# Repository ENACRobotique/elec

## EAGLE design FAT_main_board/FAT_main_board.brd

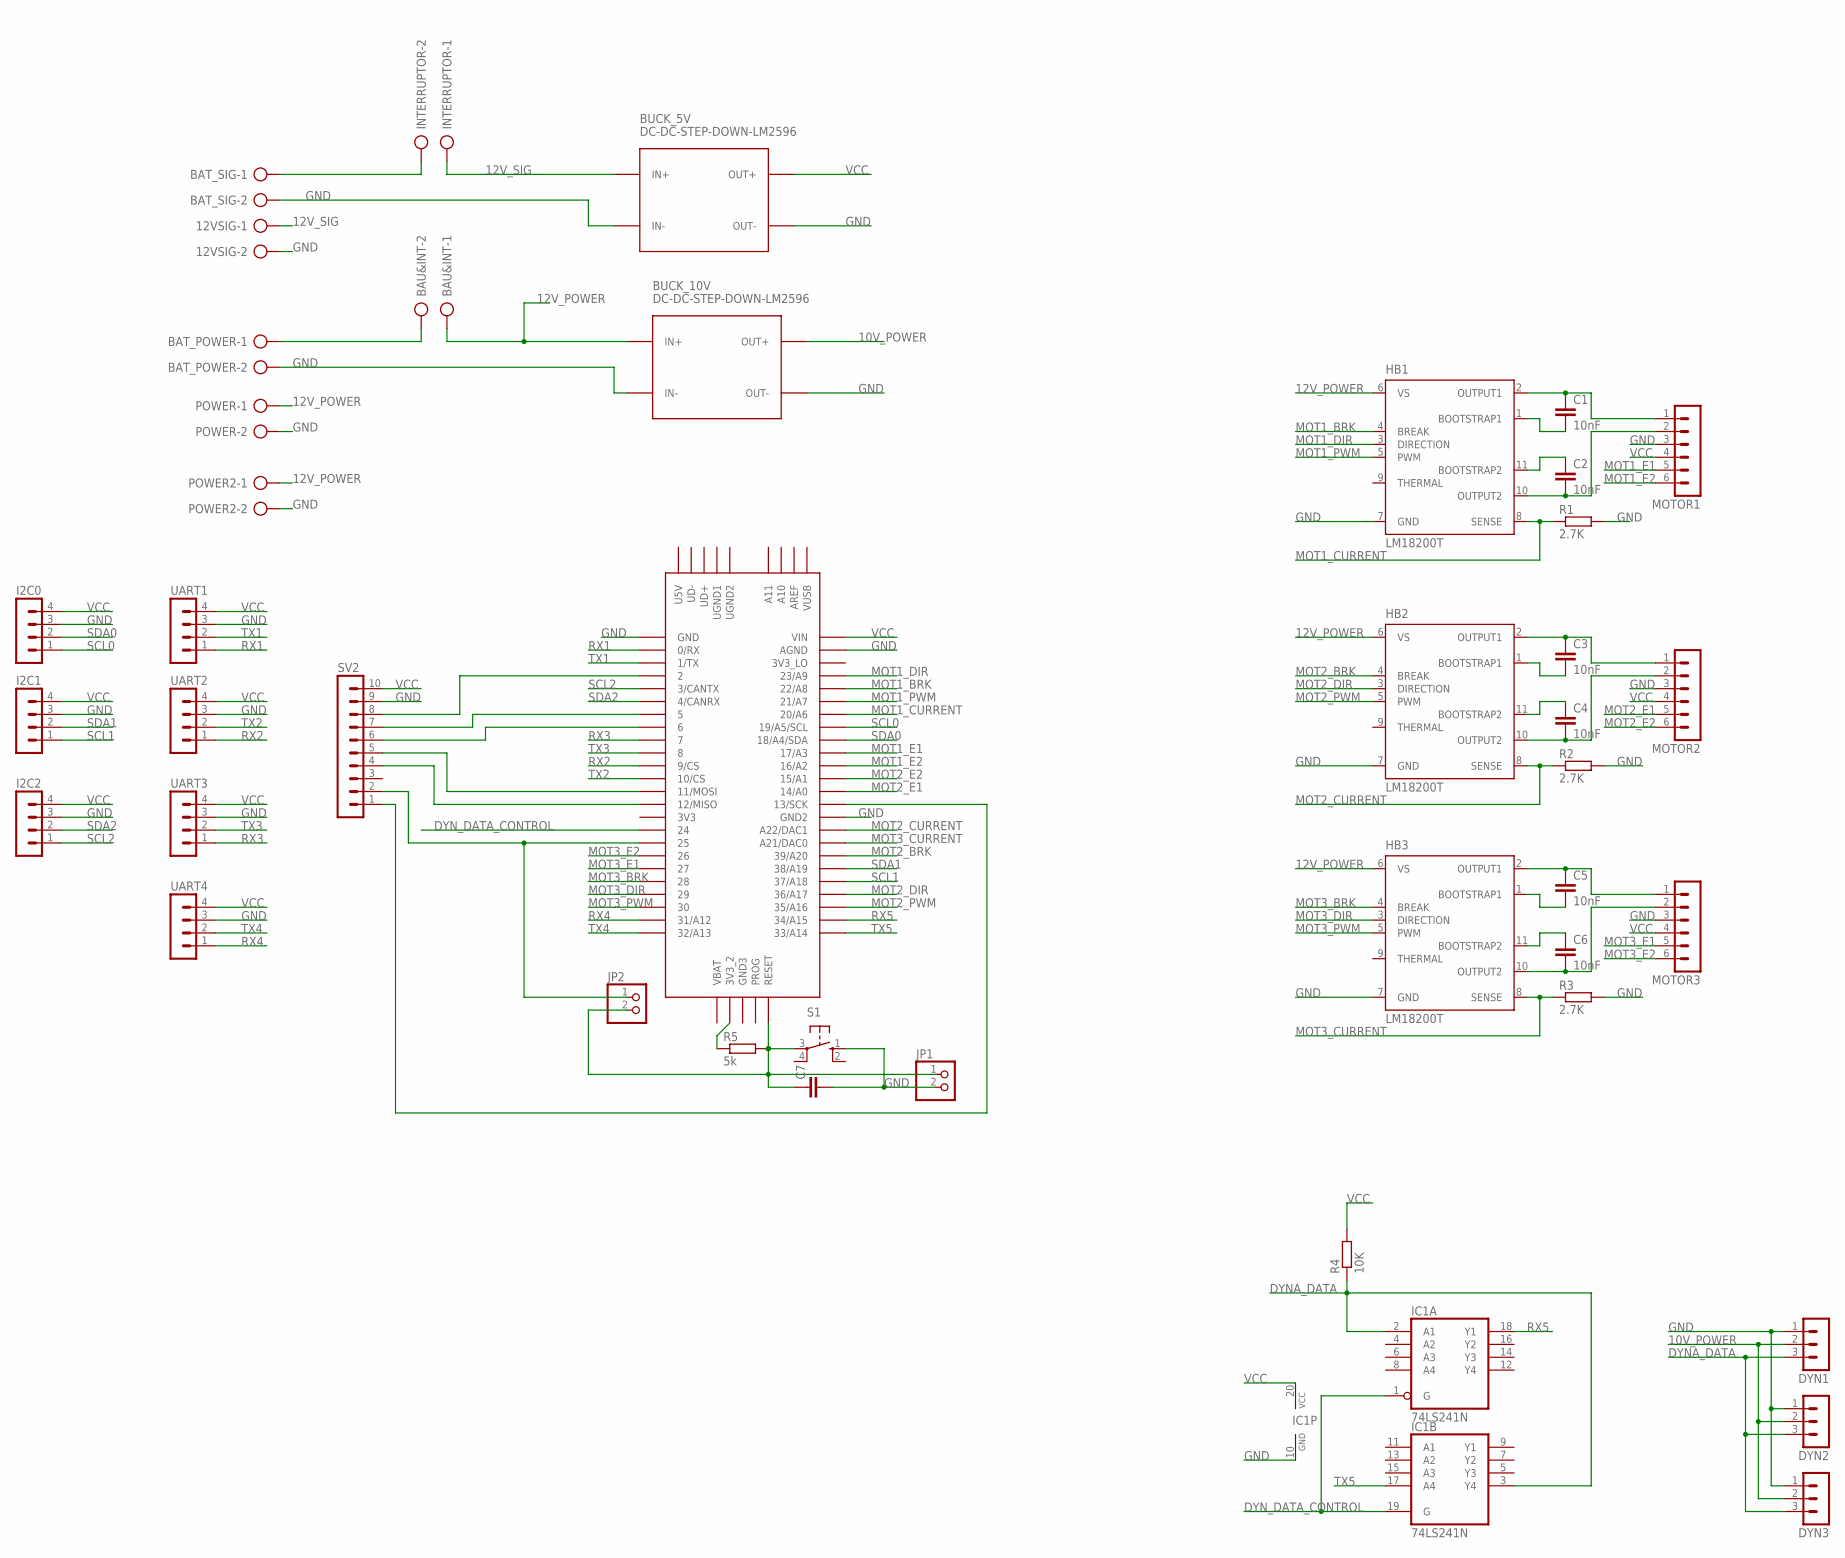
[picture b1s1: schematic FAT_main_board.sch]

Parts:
12VSIG: AK300/2
BAT_POWER: AK300/2
BAT_SIG: AK300/2
BAU&INT: AK300/2
BUCK_5V, BUCK_10V: DC-DC-STEP-DOWN-LM2596
C1, C2, C3, C4, C5, C6: 10nF; C050-035X075
C7: C-EU025-025X050; C025-025X050
DYN1, DYN2, DYN3: MA03-1
HB1, HB2, HB3: LM18200T; TO-220-11
I2C0, I2C1, I2C2: MA04-1
IC1: 74LS241N; DIL20
INTERRUPTOR: AK300/2
JP1, JP2: PINHD-1X2; 1X02
MOTOR1, MOTOR2, MOTOR3: MA06-1
POWER, POWER2: AK300/2
R1, R2, R3: 2.7K; 0204/7
R4: 10K; 0204/7
R5: 5k; 0204/7
S1: 10-XX; B3F-10XX
SV2: MA10-1
U$1: TEENSY_3.5/3.6
UART1, UART2, UART3, UART4: MA04-1

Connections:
10V_POWER: BUCK_10V.OUT+, DYN1.2, DYN2.2, DYN3.2
12V_POWER: BAU&INT.1, BUCK_10V.IN+, HB1.6 (VS), HB2.6 (VS), HB3.6 (VS), POWER.1, POWER2.1
12V_SIG: 12VSIG.1, BUCK_5V.IN+, INTERRUPTOR.1
DYNA_DATA: DYN1.3, DYN2.3, DYN3.3, IC1.2 (A1), IC1.3 (Y4), R4.1
DYN_DATA_CONTROL: IC1.1 (G), IC1.19 (G), U$1.24
GND: 12VSIG.2, BAT_POWER.2, BAT_SIG.2, BUCK_5V.IN-, BUCK_5V.OUT-, BUCK_10V.IN-, BUCK_10V.OUT-, C7.2, DYN1.1, DYN2.1, DYN3.1, HB1.7 (GND), HB2.7 (GND), HB3.7 (GND), I2C0.3, I2C1.3, I2C2.3, IC1.10 (GND), JP1.2, MOTOR1.3, MOTOR2.3, MOTOR3.3, POWER.2, POWER2.2, R1.2, R2.2, R3.2, S1.1 (S), SV2.9, U$1.AGND, U$1.GND, U$1.GND2, UART1.3, UART2.3, UART3.3, UART4.3
MOT1_BRK: HB1.4 (BREAK), U$1.22/A8
MOT1_CURRENT: HB1.8 (SENSE), R1.1, U$1.20/A6
MOT1_DIR: HB1.3 (DIRECTION), U$1.23/A9
MOT1_E1: MOTOR1.5, U$1.17/A3
MOT1_E2: MOTOR1.6, U$1.16/A2
MOT1_PWM: HB1.5 (PWM), U$1.21/A7
MOT2_BRK: HB2.4 (BREAK), U$1.39/A20
MOT2_CURRENT: HB2.8 (SENSE), R2.1, U$1.A22/DAC1
MOT2_DIR: HB2.3 (DIRECTION), U$1.36/A17
MOT2_E1: MOTOR2.5, U$1.14/A0
MOT2_E2: MOTOR2.6, U$1.15/A1
MOT2_PWM: HB2.5 (PWM), U$1.35/A16
MOT3_BRK: HB3.4 (BREAK), U$1.28
MOT3_CURRENT: HB3.8 (SENSE), R3.1, U$1.21/DAC0 (A21/DAC0)
MOT3_DIR: HB3.3 (DIRECTION), U$1.29
MOT3_E1: MOTOR3.5, U$1.27
MOT3_E2: MOTOR3.6, U$1.26
MOT3_PWM: HB3.5 (PWM), U$1.30
unnamed: C1.1, HB1.2 (OUTPUT1), MOTOR1.1
unnamed: C2.2, HB1.10 (OUTPUT2), MOTOR1.2
unnamed: C1.2, HB1.1 (BOOTSTRAP1)
unnamed: C2.1, HB1.11 (BOOTSTRAP2)
unnamed: C3.1, HB2.2 (OUTPUT1), MOTOR2.1
unnamed: C3.2, HB2.1 (BOOTSTRAP1)
unnamed: C4.1, HB2.11 (BOOTSTRAP2)
unnamed: C4.2, HB2.10 (OUTPUT2), MOTOR2.2
unnamed: SV2.7, U$1.5
unnamed: SV2.6, U$1.6
unnamed: SV2.5, U$1.11/MOSI
unnamed: SV2.4, U$1.12/MISO
unnamed: BAT_POWER.1, BAU&INT.2
unnamed: C5.1, HB3.2 (OUTPUT1), MOTOR3.1
unnamed: C5.2, HB3.1 (BOOTSTRAP1)
unnamed: C6.1, HB3.11 (BOOTSTRAP2)
unnamed: C6.2, HB3.10 (OUTPUT2), MOTOR3.2
unnamed: SV2.8, U$1.2
unnamed: C7.1, JP1.1, JP2.2, R5.2, S1.3, U$1.RESET
unnamed: BAT_SIG.1, INTERRUPTOR.2
unnamed: SV2.1, U$1.13/SCK
unnamed: R5.1, U$1.3V3_2
unnamed: JP2.1, SV2.2, U$1.25
RX1: U$1.0/RX, UART1.1
RX2: U$1.9/CS, UART2.1
RX3: U$1.7, UART3.1
RX4: U$1.31/A12, UART4.1
RX5: IC1.18 (Y1), U$1.34/A15
SCL0: I2C0.1, U$1.19/A5/SCL
SCL1: I2C1.1, U$1.37/A18
SCL2: I2C2.1, U$1.3/CANTX
SDA0: I2C0.2, U$1.18/A4/SDA
SDA1: I2C1.2, U$1.38/A19
SDA2: I2C2.2, U$1.4/CANRX
TX1: U$1.1/TX, UART1.2
TX2: U$1.10/CS, UART2.2
TX3: U$1.8, UART3.2
TX4: U$1.32/A13, UART4.2
TX5: IC1.17 (A4), U$1.33/A14
VCC: BUCK_5V.OUT+, I2C0.4, I2C1.4, I2C2.4, IC1.20 (VCC), MOTOR1.4, MOTOR2.4, MOTOR3.4, R4.2, SV2.10, U$1.VIN, UART1.4, UART2.4, UART3.4, UART4.4

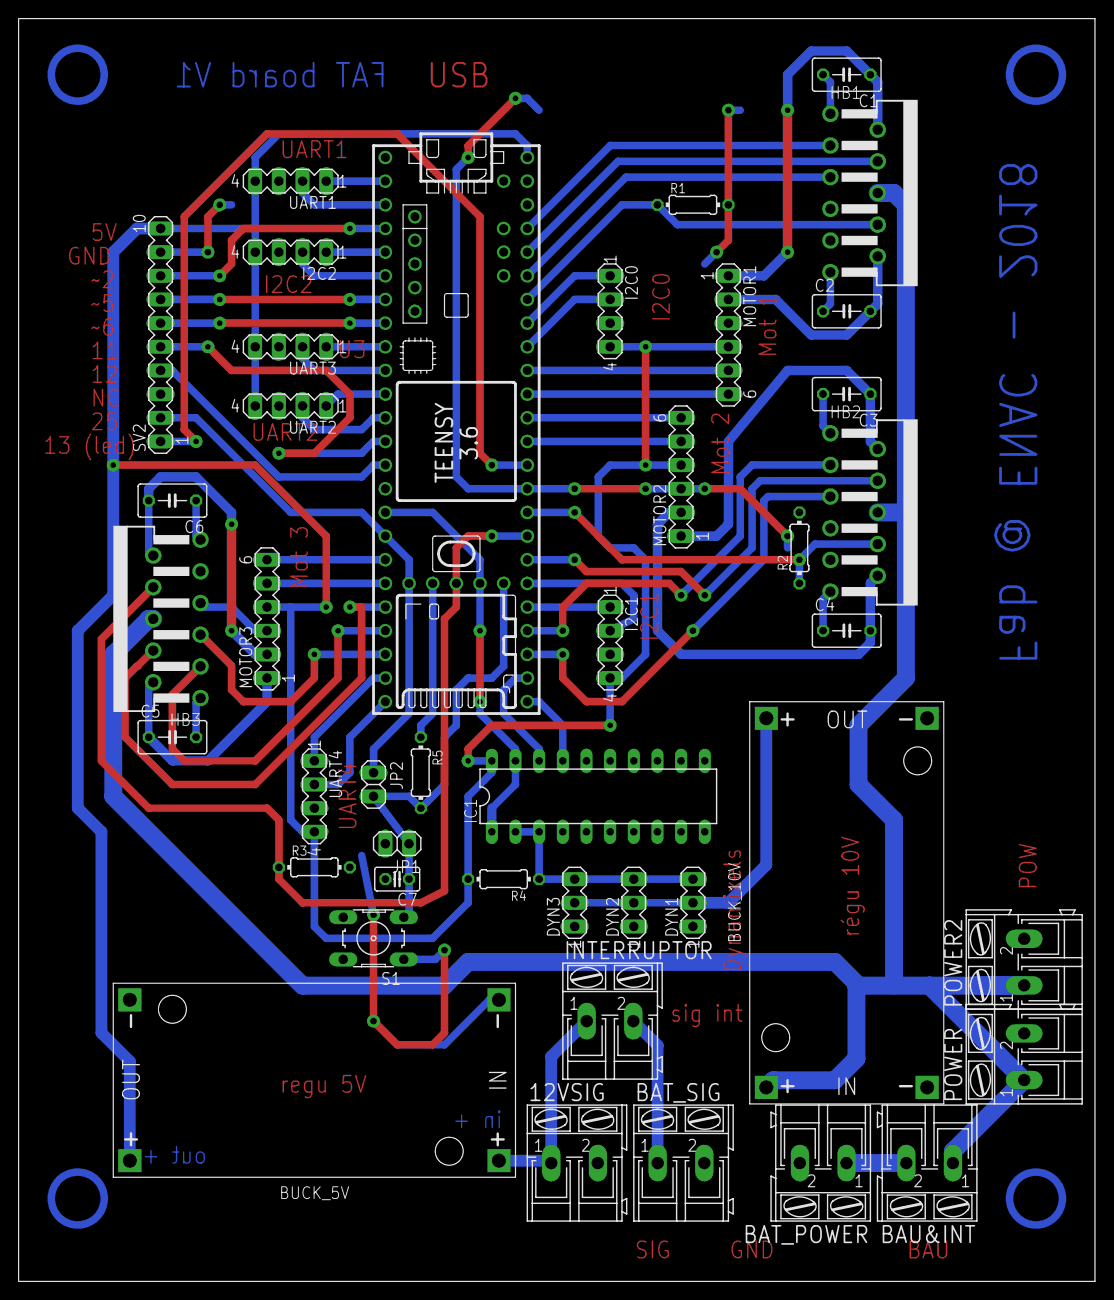
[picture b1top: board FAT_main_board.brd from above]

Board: 2 copper layers, 115.5 x 135.6 mm, 43 parts (0 on the bottom side), 64 nets.

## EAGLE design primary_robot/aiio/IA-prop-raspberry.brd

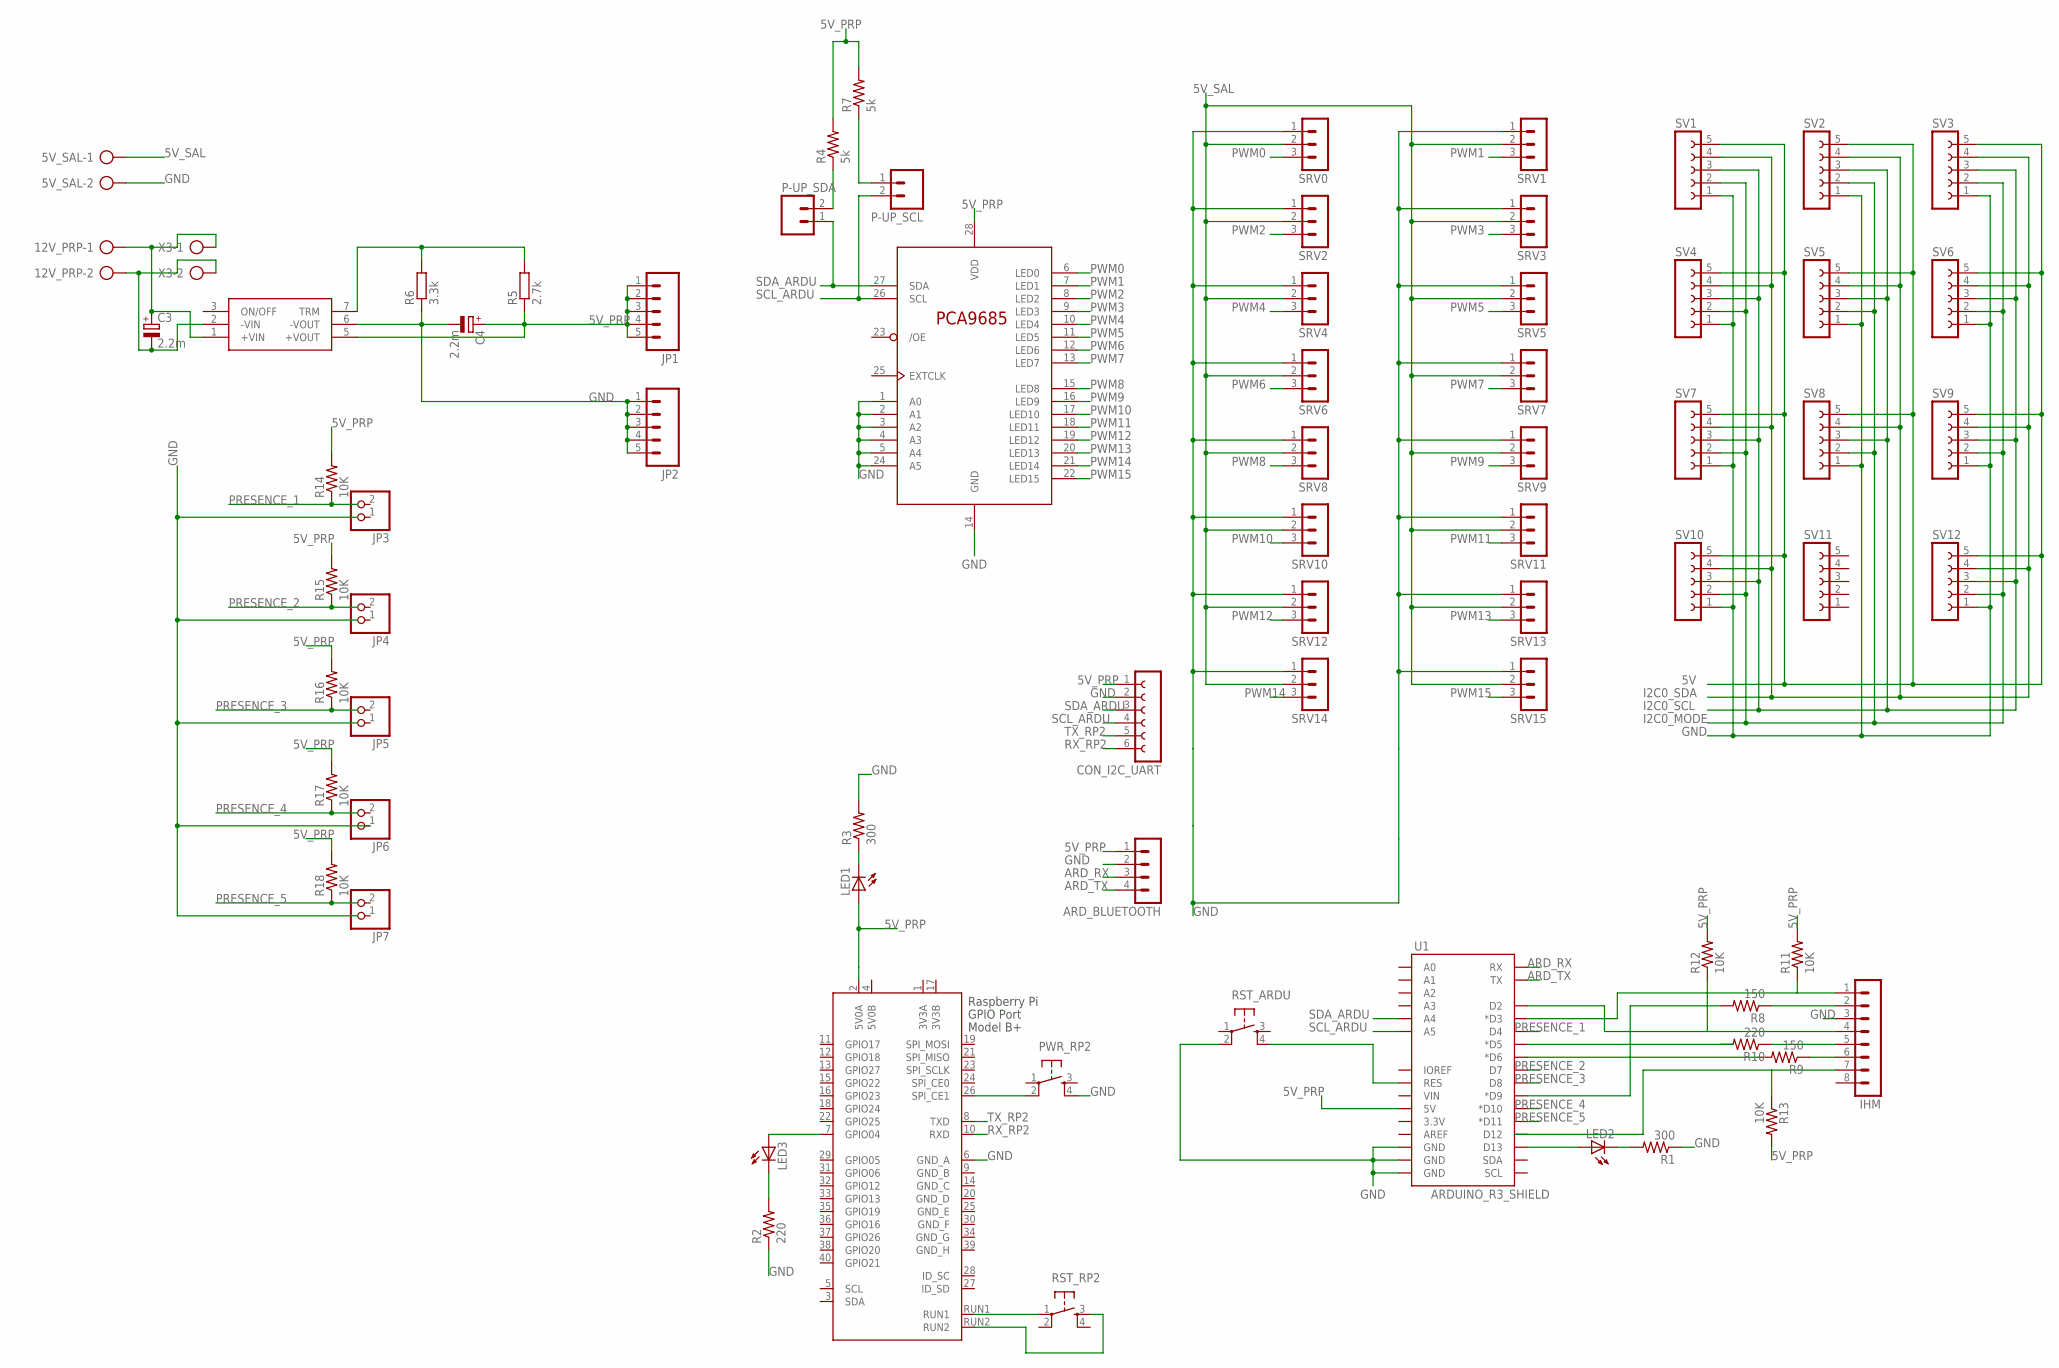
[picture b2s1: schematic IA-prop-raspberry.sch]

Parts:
5V_SAL, 12V_PRP: AK300/2
ARD_BLUETOOTH: MA04-1
C3, C4: 2.2m; E5-13
CON_I2C_UART: FE06-1; FE06
IHM: MA08-1
JP1, JP2: M05PTH; 1X05
JP3, JP4, JP5, JP6, JP7: PINHD-1X2; 1X02
LED1, LED2, LED3: LED3MM
P-UP_SCL: M02PTH; 1X02
P-UP_SDA: M02PTH; 1X02
PWR_RP2: TAC_SWITCHPTH; TACTILE-PTH
R1, R3: 300; AXIAL-0.3
R2, R10: 220; AXIAL-0.3
R4, R7: 5k; AXIAL-0.3
R5: 2.7k; 0207/7
R6: 3.3k; 0207/7
R8, R9: 150; AXIAL-0.3
R11, R12, R13, R14, R15, R16, R17, R18: 10K; AXIAL-0.3
RP2: RASPI_BOARD_B+#_FP; RASPI_BOARD_B+_FULL_PAD
RST_ARDU: TAC_SWITCHPTH; TACTILE-PTH
RST_RP2: TAC_SWITCHPTH; TACTILE-PTH
SRV0, SRV1, SRV2, SRV3, SRV4, SRV5, SRV6, SRV7, SRV8, SRV9, SRV10, SRV11, SRV12, SRV13, SRV14, SRV15: MA03-1
SV1, SV2, SV3, SV4, SV5, SV6, SV7, SV8, SV9, SV10, SV11, SV12: FE05-1
U1: ARDUINO_R3_SHIELD; UNO_R3_SHIELD
U$1: PCA9685PW; TSSOP28
U$2: TEN25-1211TEN25-1211; TEN25
X3: AK300/2

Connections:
3V3A: RP2.1 (3V3A)
3V3B: RP2.17 (3V3B)
5V: SV1.5, SV2.5, SV3.5, SV4.5, SV5.5, SV6.5, SV7.5, SV8.5, SV9.5, SV10.5, SV12.5
5V0B: RP2.4 (5V0B)
5V_PRP: ARD_BLUETOOTH.1, C4.+, CON_I2C_UART.1, JP1.1, JP1.2, JP1.3, JP1.4, JP1.5, LED1.A, R4.P$2 (2), R5.1, R7.P$2 (2), R11.P$2 (2), R12.P$2 (2), R13.P$2 (2), R14.P$2 (2), R15.P$2 (2), R16.P$2 (2), R17.P$2 (2), R18.P$2 (2), RP2.2 (5V0A), U1.5V, U$1.28 (VDD), U$2.5 (+VOUT)
5V_PRP1: LED2.A, U1.D13
5V_SAL: 5V_SAL.1, SRV0.2, SRV1.2, SRV2.2, SRV3.2, SRV4.2, SRV5.2, SRV6.2, SRV7.2, SRV8.2, SRV9.2, SRV10.2, SRV11.2, SRV12.2, SRV13.2, SRV14.2, SRV15.2
+12V: 12V_PRP.1, C3.+, U$2.1 (+VIN), X3.1
ARD_RX: ARD_BLUETOOTH.3, U1.RX
ARD_TX: ARD_BLUETOOTH.4, U1.TX
GND: 5V_SAL.2, ARD_BLUETOOTH.2, C4.-, CON_I2C_UART.2, IHM.3, JP2.1, JP2.2, JP2.3, JP2.4, JP2.5, JP6.1, PWR_RP2.4, R1.P$1 (1), R2.P$1 (1), R3.P$2 (2), R6.1, RP2.6 (GND_A), RST_ARDU.2, SRV0.1, SRV1.1, SRV2.1, SRV3.1, SRV4.1, SRV5.1, SRV6.1, SRV7.1, SRV8.1, SRV9.1, SRV10.1, SRV11.1, SRV12.1, SRV13.1, SRV14.1, SRV15.1, SV1.1, SV2.1, SV3.1, SV4.1, SV5.1, SV6.1, SV7.1, SV8.1, SV9.1, SV10.1, SV12.1, U1.GND@0 (GND), U1.GND@1 (GND), U1.GND@2 (GND), U$1.1 (A0), U$1.2 (A1), U$1.3 (A2), U$1.4 (A3), U$1.5 (A4), U$1.14 (GND), U$1.24 (A5), U$2.6 (-VOUT)
GND_12: 12V_PRP.2, C3.-, U$2.2 (-VIN), X3.2
GND_B: RP2.9 (GND_B)
GND_C: RP2.14 (GND_C)
GND_D: RP2.20 (GND_D)
GND_E: RP2.25 (GND_E)
GND_F: RP2.30 (GND_F)
GND_G: RP2.34 (GND_G)
GND_H: RP2.39 (GND_H)
I2C0_MODE: SV1.2, SV2.2, SV3.2, SV4.2, SV5.2, SV6.2, SV7.2, SV8.2, SV9.2, SV10.2, SV12.2
I2C0_SCL: SV1.3, SV2.3, SV3.3, SV4.3, SV5.3, SV6.3, SV7.3, SV8.3, SV9.3, SV10.3, SV12.3
I2C0_SDA: SV1.4, SV2.4, SV3.4, SV4.4, SV5.4, SV6.4, SV7.4, SV8.4, SV9.4, SV10.4, SV12.4
unnamed: RP2.RUN2, RST_RP2.3
unnamed: LED2.K (C), R1.P$2 (2)
unnamed: LED3.K (C), R2.P$2 (2)
unnamed: R5.2, R6.2, U$2.7 (TRM)
unnamed: P-UP_SDA.2, R4.P$1 (1)
unnamed: LED1.K (C), R3.P$1 (1)
unnamed: RST_ARDU.4, U1.RES
unnamed: P-UP_SCL.1, R7.P$1 (1)
unnamed: R9.P$2 (2), U1.D6 (*D6)
unnamed: IHM.6, R9.P$1 (1)
unnamed: LED3.A, RP2.7 (GPIO04)
unnamed: IHM.5, R10.P$1 (1)
unnamed: IHM.2, R8.P$1 (1)
unnamed: R8.P$2 (2), U1.D9 (*D9)
unnamed: IHM.1, R11.P$1 (1), U1.D3 (*D3)
unnamed: IHM.4, R12.P$1 (1), U1.D2
unnamed: RP2.RUN1, RST_RP2.1
unnamed: IHM.7, R13.P$1 (1)
PRESENCE_1: R14.P$1 (1), U1.D4
PRESENCE_2: R15.P$1 (1), U1.D7
PRESENCE_3: R16.P$1 (1), U1.D8
PRESENCE_4: R17.P$1 (1), U1.D10 (*D10)
PRESENCE_5: R18.P$1 (1), U1.D11 (*D11)
PWM0: SRV0.3, U$1.6 (LED0)
PWM1: SRV1.3, U$1.7 (LED1)
PWM2: SRV2.3, U$1.8 (LED2)
PWM3: SRV3.3, U$1.9 (LED3)
PWM4: SRV4.3, U$1.10 (LED4)
PWM5: SRV5.3, U$1.11 (LED5)
PWM6: SRV6.3, U$1.12 (LED6)
PWM7: SRV7.3, U$1.13 (LED7)
PWM8: SRV8.3, U$1.15 (LED8)
PWM9: SRV9.3, U$1.16 (LED9)
PWM10: SRV10.3, U$1.17 (LED10)
PWM11: SRV11.3, U$1.18 (LED11)
PWM12: SRV12.3, U$1.19 (LED12)
PWM13: SRV13.3, U$1.20 (LED13)
PWM14: SRV14.3, U$1.21 (LED14)
PWM15: SRV15.3, U$1.22 (LED15)
RP2_PWR: PWR_RP2.2, RP2.26 (SPI_CE1)
RX_RP2: CON_I2C_UART.6, RP2.10 (RXD)
SCL_ARDU: CON_I2C_UART.4, P-UP_SCL.2, U1.A5, U$1.26 (SCL)
SDA_ARDU: CON_I2C_UART.3, P-UP_SDA.1, U1.A4, U$1.27 (SDA)
TX_RP2: CON_I2C_UART.5, RP2.8 (TXD)

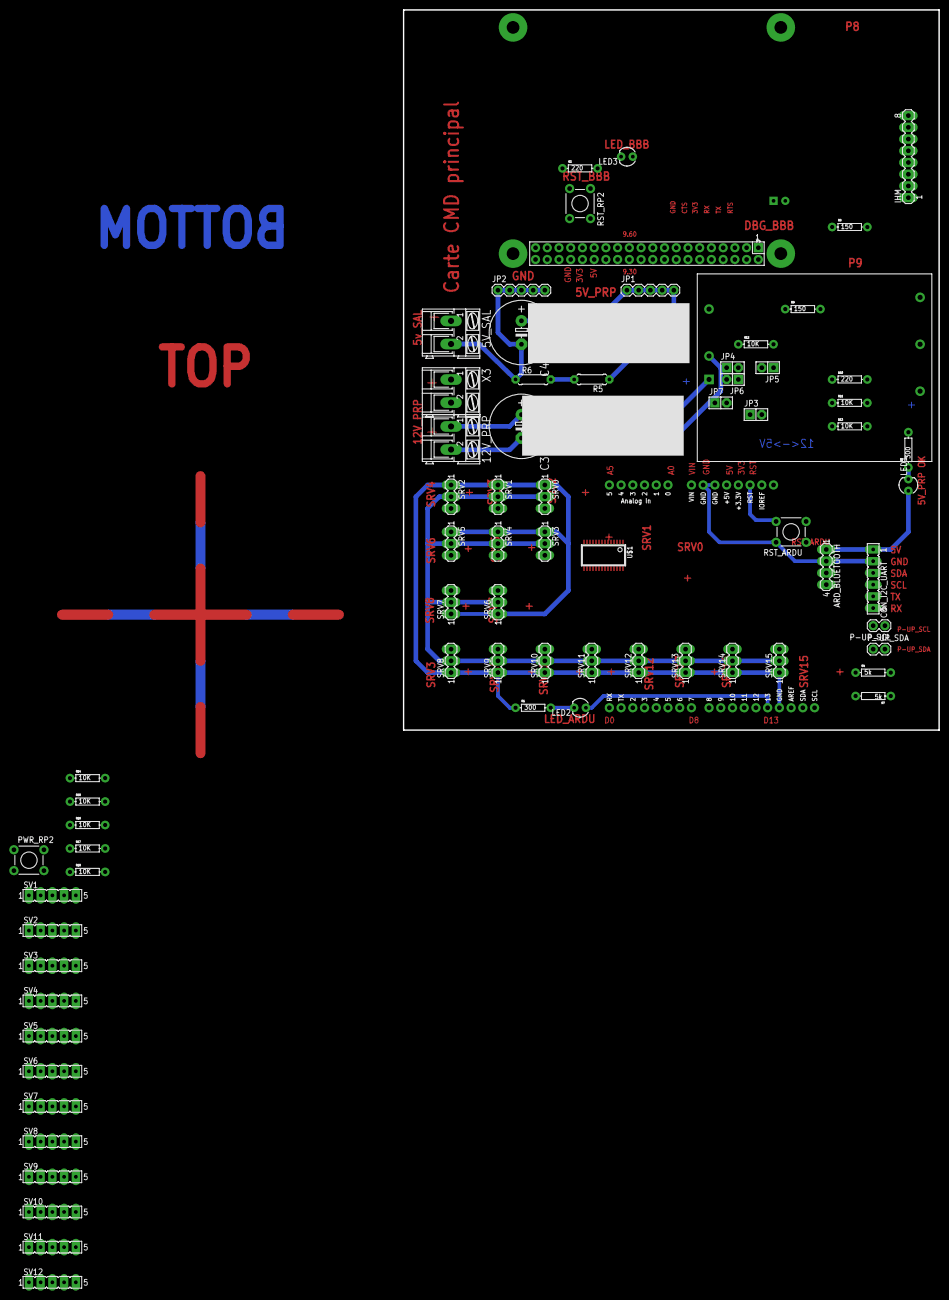
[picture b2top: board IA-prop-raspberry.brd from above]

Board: 2 copper layers, 116.0 x 156.0 mm, 73 parts (0 on the bottom side), 56 nets.

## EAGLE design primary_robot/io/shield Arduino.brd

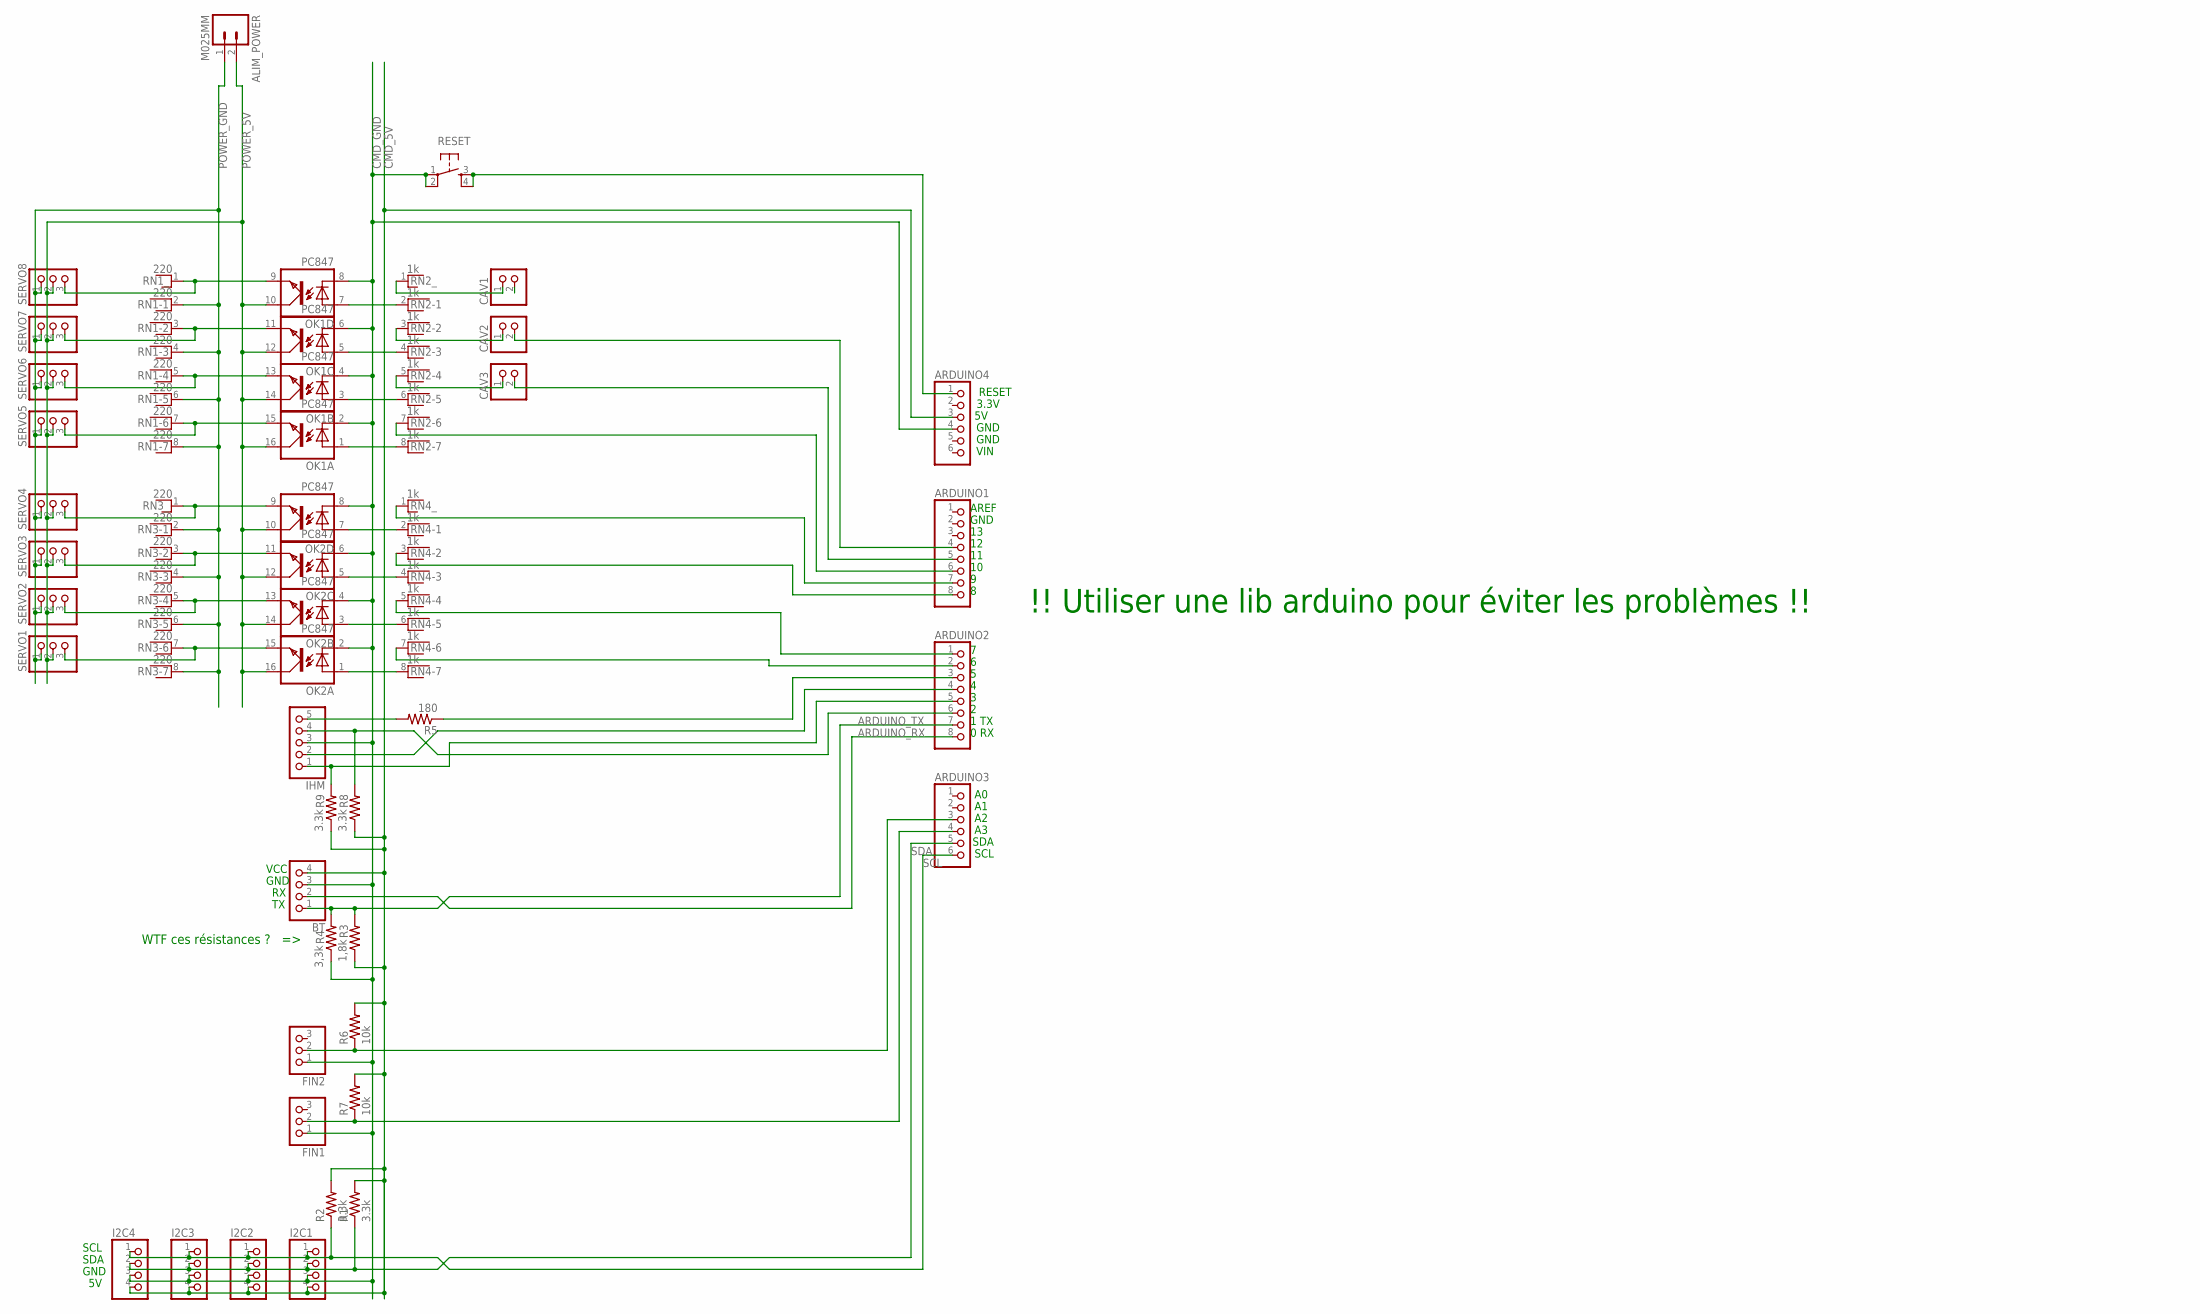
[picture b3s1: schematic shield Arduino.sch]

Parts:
ALIM_POWER: M025MM; SCREWTERMINAL-5MM-2
ARDUINO1, ARDUINO2: PINHD-1X8; 1X08
ARDUINO3, ARDUINO4: PINHD-1X6; 1X06
BT: PINHD-1X4; 1X04
CAV1, CAV2, CAV3: PINHD-1X2; 1X02
FIN1, FIN2: PINHD-1X3; 1X03
I2C1, I2C2, I2C3, I2C4: PINHD-1X4; 1X04
IHM: PINHD-1X5; 1X05
OK1, OK2: PC847; DIL16
R1, R2, R8, R9: 3.3k; 0204/7
R3: 1,8k; 0204/7
R4: 3,3k; 0204/7
R5: 180; 0204/7
R6, R7: 10k; 0204/7
RESET: TAC_SWITCHPTH; TACTILE-PTH
RN1, RN3: 220; RN-8
RN2, RN4: 1k; RN-8
SERVO1, SERVO2, SERVO3, SERVO4, SERVO5, SERVO6, SERVO7, SERVO8: PINHD-1X3; 1X03

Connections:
ARDUINO_RX: ARDUINO2.8, BT.2
ARDUINO_TX: ARDUINO2.7, BT.1, R3.2, R4.2
CMD_5V: ARDUINO4.3, BT.4, I2C1.4, I2C2.4, I2C3.4, I2C4.4, R1.2, R2.2, R3.1, R6.2, R7.2, R8.1, R9.1
CMD_GND: ARDUINO4.4, BT.3, FIN1.1, FIN2.1, I2C1.3, I2C2.3, I2C3.3, I2C4.3, IHM.3, OK1.2 (C), OK1.4 (C), OK1.6 (C), OK1.8 (C), OK2.2 (C), OK2.4 (C), OK2.6 (C), OK2.8 (C), R4.1, RESET.1, RESET.2
unnamed: OK2.7 (A), RN4.2
unnamed: ARDUINO1.4, CAV2.2
unnamed: OK2.5 (A), RN4.4
unnamed: OK2.3 (A), RN4.6
unnamed: OK1.15 (EMIT), RN1.7, SERVO5.3
unnamed: OK1.9 (EMIT), RN1.1, SERVO8.3
unnamed: ARDUINO1.5, CAV3.2
unnamed: OK2.1 (A), RN4.8
unnamed: OK1.11 (EMIT), RN1.3, SERVO7.3
unnamed: OK1.13 (EMIT), RN1.5, SERVO6.3
unnamed: OK1.1 (A), RN2.8
unnamed: OK1.3 (A), RN2.6
unnamed: OK1.5 (A), RN2.4
unnamed: OK1.7 (A), RN2.2
unnamed: CAV1.1, RN2.1
unnamed: CAV2.1, RN2.3
unnamed: CAV3.1, RN2.5
unnamed: ARDUINO1.6, RN2.7
unnamed: OK2.15 (EMIT), RN3.7, SERVO1.3
unnamed: OK2.9 (EMIT), RN3.1, SERVO4.3
unnamed: OK2.11 (EMIT), RN3.3, SERVO3.3
unnamed: OK2.13 (EMIT), RN3.5, SERVO2.3
unnamed: ARDUINO4.1, RESET.3, RESET.4
unnamed: ARDUINO1.7, RN4.1
unnamed: ARDUINO1.8, RN4.3
unnamed: ARDUINO2.1, RN4.5
unnamed: ARDUINO2.2, RN4.7
unnamed: IHM.5, R5.2
unnamed: ARDUINO3.4, FIN1.2, R7.1
unnamed: ARDUINO3.3, FIN2.2, R6.1
unnamed: ARDUINO2.3, R5.1
unnamed: ARDUINO2.5, IHM.1, R9.2
unnamed: ARDUINO2.4, IHM.2
unnamed: ARDUINO2.6, IHM.4, R8.2
POWER_5V: ALIM_POWER.2, OK1.10 (COL), OK1.12 (COL), OK1.14 (COL), OK1.16 (COL), OK2.10 (COL), OK2.12 (COL), OK2.14 (COL), OK2.16 (COL), SERVO1.2, SERVO2.2, SERVO3.2, SERVO4.2, SERVO5.2, SERVO6.2, SERVO7.2, SERVO8.2
POWER_GND: ALIM_POWER.1, RN1.2, RN1.4, RN1.6, RN1.8, RN3.2, RN3.4, RN3.6, RN3.8, SERVO1.1, SERVO2.1, SERVO3.1, SERVO4.1, SERVO5.1, SERVO6.1, SERVO7.1, SERVO8.1
SCL: ARDUINO3.6, I2C1.1, I2C2.1, I2C3.1, I2C4.1, R2.1
SDA: ARDUINO3.5, I2C1.2, I2C2.2, I2C3.2, I2C4.2, R1.1

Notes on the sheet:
SDA
SCL
0 RX
1 TX
GND
AREF
VIN
3.3V
RESET
VCC
!! Utiliser une lib arduino pour éviter les problèmes !!
WTF ces résistances ? =>

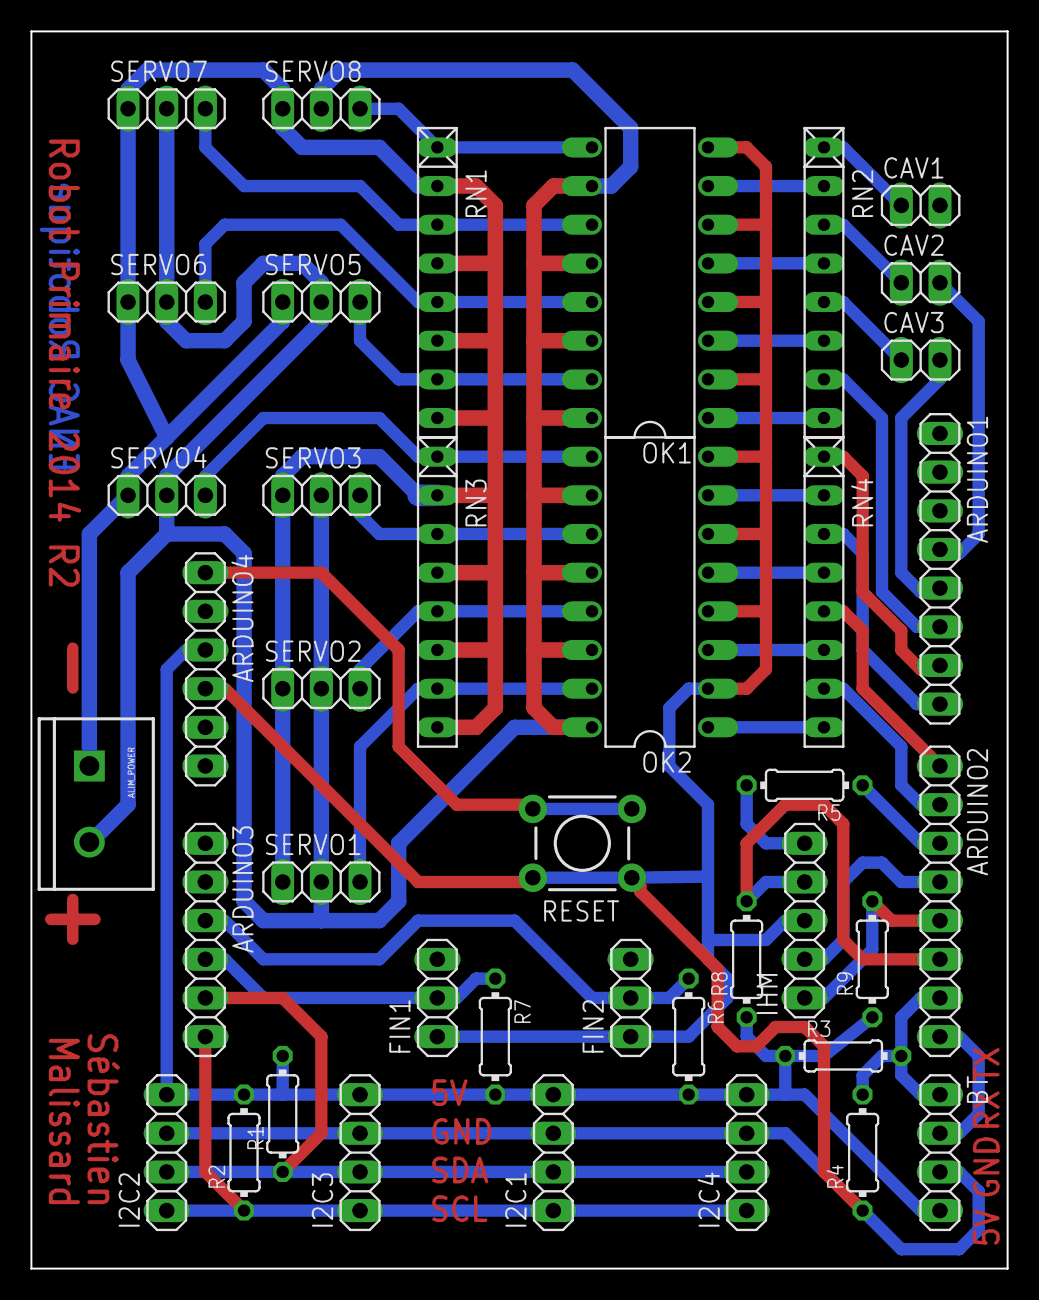
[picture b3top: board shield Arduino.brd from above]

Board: 2 copper layers, 64.1 x 81.3 mm, 40 parts (0 on the bottom side), 42 nets.

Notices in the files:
parts and their libraries:
diy-modules: Released under the Creative Commons Attribution 4.0 International License: http://creativecommons.org/licenses/by/4.0
SparkFun: Licensing: CC v3.0 Share-Alike You are welcome to use this library for commercial purposes.
